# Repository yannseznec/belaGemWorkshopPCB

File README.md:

# belaGemWorkshopPCB

## A PCB designed for the Bela Gem

This board is meant to be a general-purpose PCB, specifically suited to how I use the Bela Gem. I call it a "workshop" PCB, with that idea that maybe I could use it for workshops one day? That would be fun.

In practice, this is essentially a breakout board for all of the analog and digital pins. Each of these is accessible using individual Molex (or generic 2.54") connectors. So you can use as many or as few as you need for any given project.

The Bela Gem has built-in 1/8" input and output connectors. This PCB also has Molex pins for unbalanced stereo inputs and balanced stereo outputs. The headphone output is also available as a three pin molex.

If you want to power the board via a power supply (rather than USB), there is a pin pair that is +/-. The power runs through a pair of pins labeled "Power Switch". If you don't want to use a switch, bridge these pins. If you use USB power the switch pins do nothing at all.

## To-do:

- test this! I still haven't soldered one up.
- add silkscreen labels for the power pins (to show which side is power)
- add silkscreen labels for one analog molex (to show which pins are what)
- add silkscreen labels for one digital molex (to show which pins are what)
- add silkscreen labels for audio inputs and outputs (starting to see a theme here)
- mounting holes could probably be M3 (instead of M4, i'm not sure why they are M4 that seems enormous)
- reverse the L/R on the headphone output
- reverse the power/ground on the power pins

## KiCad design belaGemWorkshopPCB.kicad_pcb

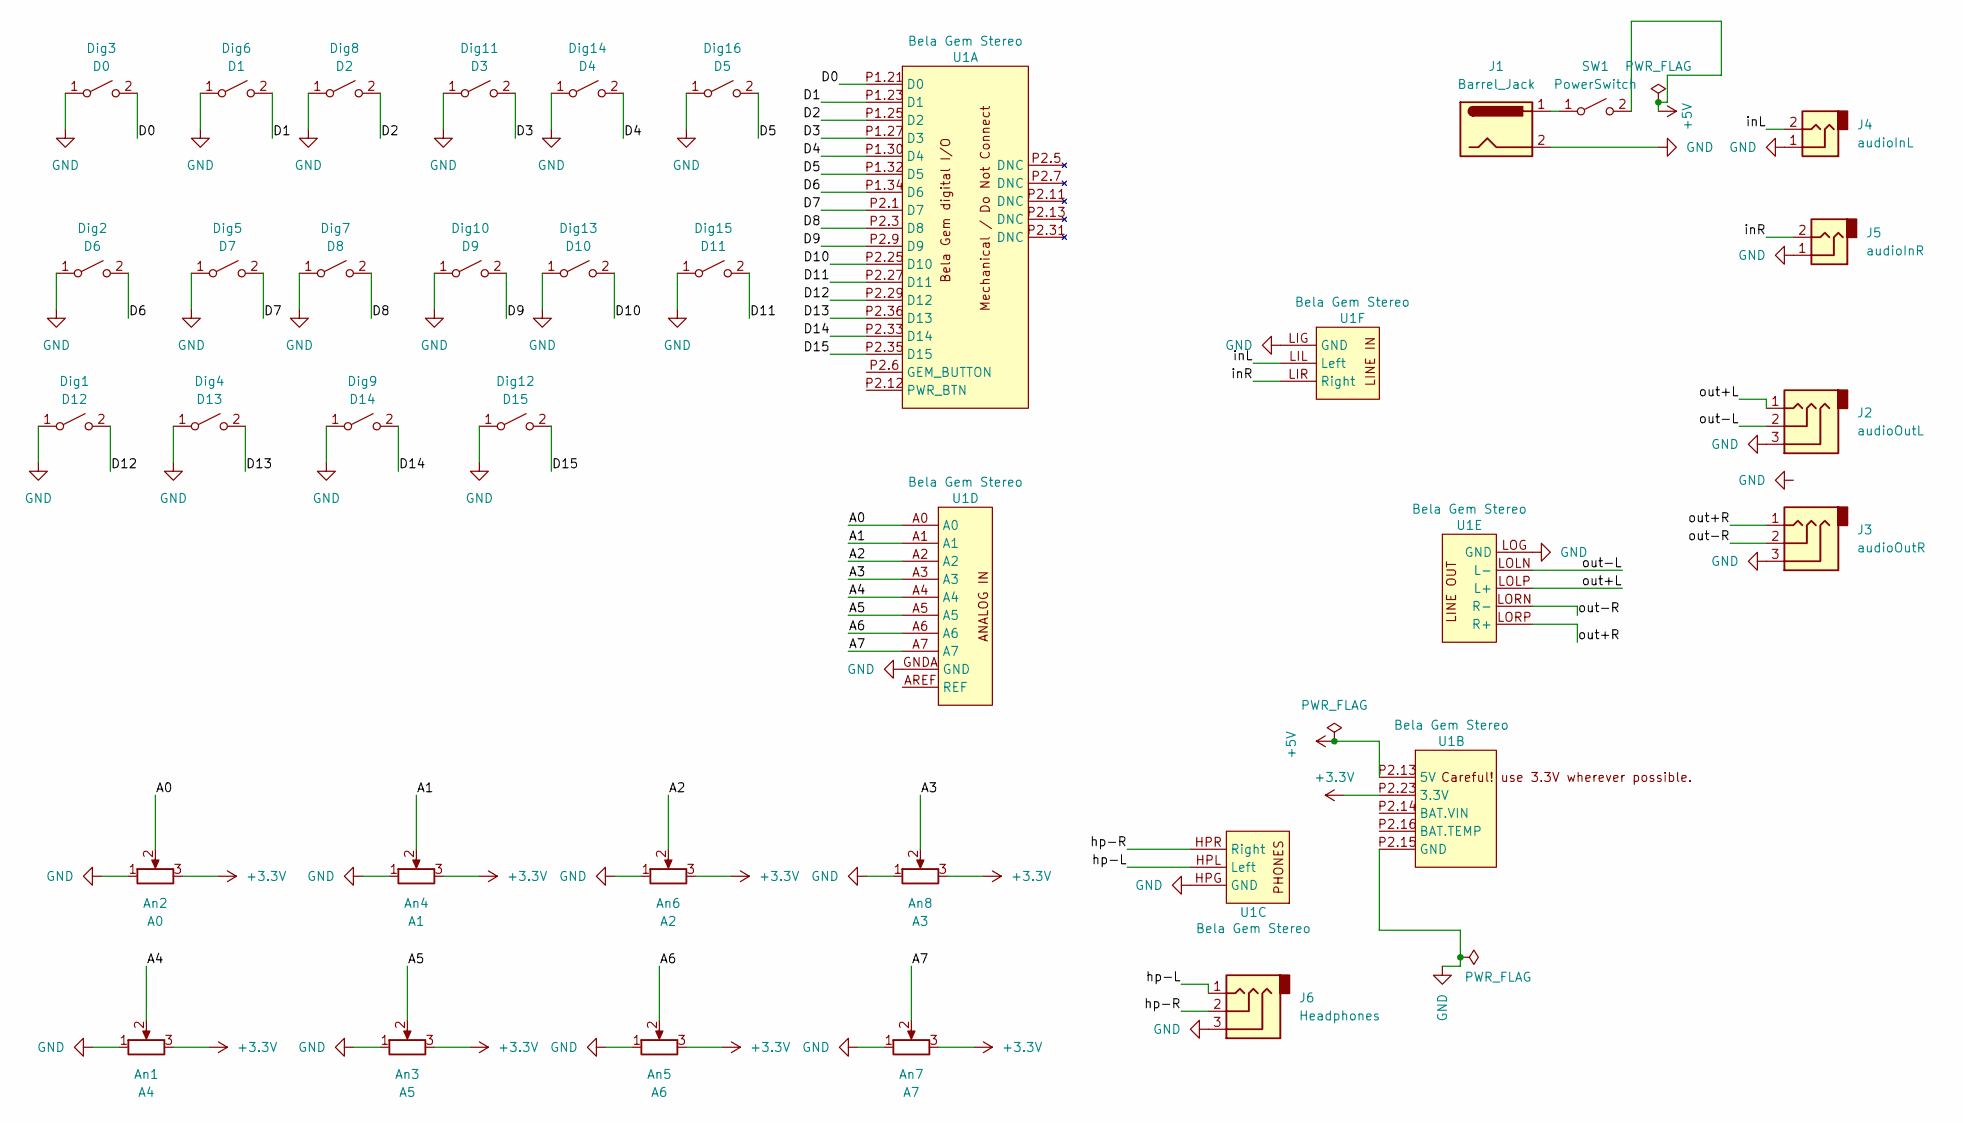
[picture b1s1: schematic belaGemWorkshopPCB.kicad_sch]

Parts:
An1: A4; Molex_KK-254_03_pin
An2: A0; Molex_KK-254_03_pin
An3: A5; Molex_KK-254_03_pin
An4: A1; Molex_KK-254_03_pin
An5: A6; Molex_KK-254_03_pin
An6: A2; Molex_KK-254_03_pin
An7: A7; Molex_KK-254_03_pin
An8: A3; Molex_KK-254_03_pin
Dig1: D12; Molex_KK-254_02_pin
Dig2: D6; Molex_KK-254_02_pin
Dig3: D0; Molex_KK-254_02_pin
Dig4: D13; Molex_KK-254_02_pin
Dig5: D7; Molex_KK-254_02_pin
Dig6: D1; Molex_KK-254_02_pin
Dig7: D8; Molex_KK-254_02_pin
Dig8: D2; Molex_KK-254_02_pin
Dig9: D14; Molex_KK-254_02_pin
Dig10: D9; Molex_KK-254_02_pin
Dig11: D3; Molex_KK-254_02_pin
Dig12: D15; Molex_KK-254_02_pin
Dig13: D10; Molex_KK-254_02_pin
Dig14: D4; Molex_KK-254_02_pin
Dig15: D11; Molex_KK-254_02_pin
Dig16: D5; Molex_KK-254_02_pin
J1: Barrel_Jack; Molex_KK-254_02_pin
J2: audioOutL; Molex_KK-254_03_pin
J3: audioOutR; Molex_KK-254_03_pin
J4: audioInL; Molex_KK-254_02_pin
J5: audioInR; Molex_KK-254_02_pin
J6: Headphones; Molex_KK-254_03_pin
SW1: PowerSwitch; Molex_KK-254_02_pin
U1: Bela Gem Stereo; Bela-Gem-stereo_advanced

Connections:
+3.3V: An1.3, An2.3, An3.3, An4.3, An5.3, An6.3, An7.3, An8.3, U1.P2.23 (3.3V)
+5V: SW1.2 (B), U1.P2.13 (5V)
/A0: An2.2, U1.A0
/A1: An4.2, U1.A1
/A2: An6.2, U1.A2
/A3: An8.2, U1.A3
/A4: An1.2, U1.A4
/A5: An3.2, U1.A5
/A6: An5.2, U1.A6
/A7: An7.2, U1.A7
/D0: Dig3.2 (B), U1.P1.21 (D0)
/D1: Dig6.2 (B), U1.P1.23 (D1)
/D2: Dig8.2 (B), U1.P1.25 (D2)
/D3: Dig11.2 (B), U1.P1.27 (D3)
/D4: Dig14.2 (B), U1.P1.30 (D4)
/D5: Dig16.2 (B), U1.P1.32 (D5)
/D6: Dig2.2 (B), U1.P1.34 (D6)
/D7: Dig5.2 (B), U1.P2.1 (D7)
/D8: Dig7.2 (B), U1.P2.3 (D8)
/D9: Dig10.2 (B), U1.P2.9 (D9)
/D10: Dig13.2 (B), U1.P2.25 (D10)
/D11: Dig15.2 (B), U1.P2.27 (D11)
/D12: Dig1.2 (B), U1.P2.29 (D12)
/D13: Dig4.2 (B), U1.P2.36 (D13)
/D14: Dig9.2 (B), U1.P2.33 (D14)
/D15: Dig12.2 (B), U1.P2.35 (D15)
/hp-L: J6.1, U1.HPL (Left)
/hp-R: J6.2, U1.HPR (Right)
/inL: J4.2, U1.LIL (Left)
/inR: J5.2, U1.LIR (Right)
/out+L: J2.1, U1.LOLP (L+)
/out+R: J3.1, U1.LORP (R+)
/out-L: J2.2, U1.LOLN (L-)
/out-R: J3.2, U1.LORN (R-)
GND: An1.1, An2.1, An3.1, An4.1, An5.1, An6.1, An7.1, An8.1, Dig1.1 (A), Dig2.1 (A), Dig3.1 (A), Dig4.1 (A), Dig5.1 (A), Dig6.1 (A), Dig7.1 (A), Dig8.1 (A), Dig9.1 (A), Dig10.1 (A), Dig11.1 (A), Dig12.1 (A), Dig13.1 (A), Dig14.1 (A), Dig15.1 (A), Dig16.1 (A), J1.2, J2.3, J3.3, J4.1, J5.1, J6.3, U1.GNDA (GND), U1.HPG (GND), U1.LIG (GND), U1.LOG (GND), U1.P2.15 (GND)
unnamed: J1.1, SW1.1 (A)

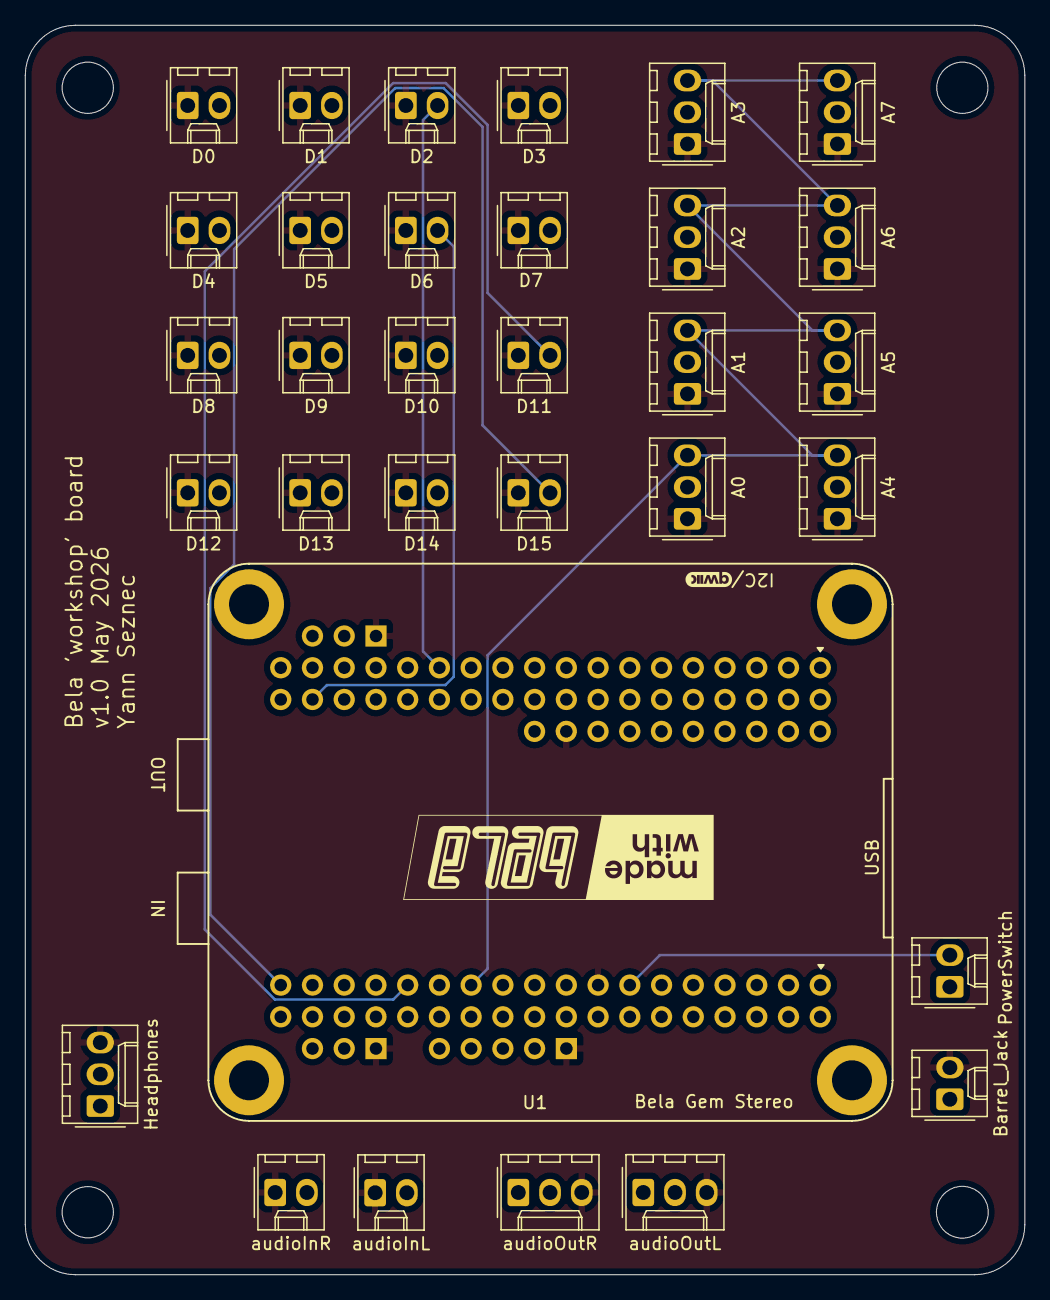
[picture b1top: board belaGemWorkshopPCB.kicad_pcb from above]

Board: 4 copper layers, 80.0 x 100.0 mm, 32 parts (0 on the bottom side), 36 nets.
